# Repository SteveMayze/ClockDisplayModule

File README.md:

# ClockDisplayModule
A module to provide a 4x7 Segment display digital clock face

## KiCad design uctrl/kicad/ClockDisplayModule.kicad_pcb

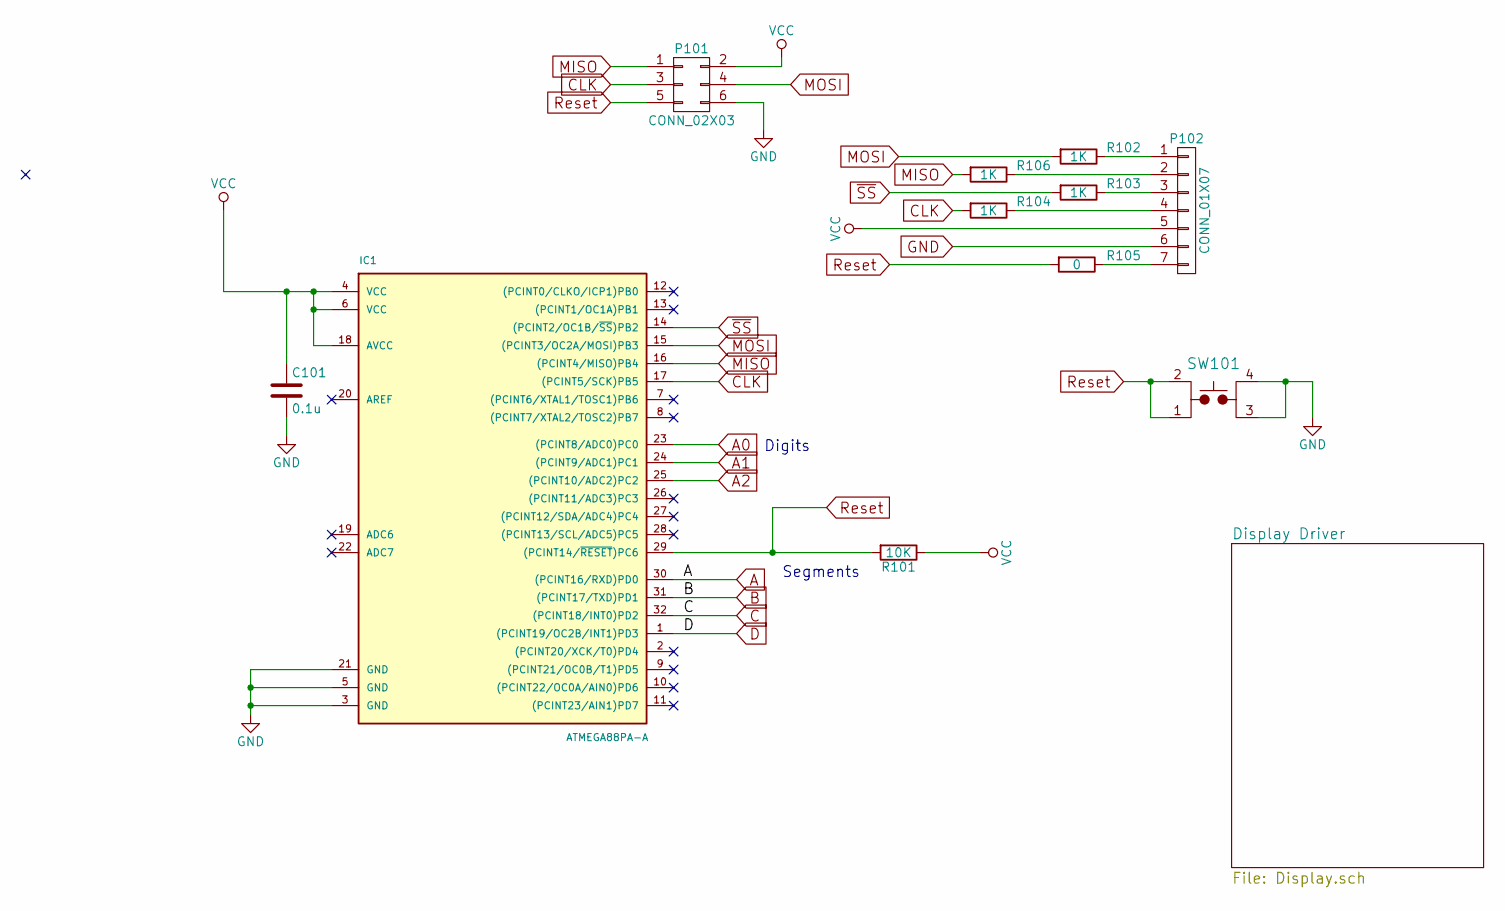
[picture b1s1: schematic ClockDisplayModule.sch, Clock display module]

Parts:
C101: 0.1u; C_0805
IC1: ATMEGA88PA-A; LQFP-32_7x7mm_Pitch0.8mm
P101: CONN_02X03; Pin_Header_Straight_2x03; MPN WS6G
P102: CONN_01X07; Pin_Header_Straight_1x07; Voltage Value; DigiKeyPN Value
R101: 10K; R_0805
R102, R103, R104, R106: 1K; R_0805
R105: 0; R_0805
SW101: TL3315NF160Q; PTS525SM15SMTR2LFS

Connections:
A: IC1.30 ((PCINT16/RXD)PD0); also elsewhere on the board
A0: IC1.23 ((PCINT8/ADC0)PC0); also elsewhere on the board
A1: IC1.24 ((PCINT9/ADC1)PC1); also elsewhere on the board
A2: IC1.25 ((PCINT10/ADC2)PC2); also elsewhere on the board
B: IC1.31 ((PCINT17/TXD)PD1); also elsewhere on the board
C: IC1.32 ((PCINT18/INT0)PD2); also elsewhere on the board
CLK: IC1.17 ((PCINT5/SCK)PB5), P101.3, R104.2
D: IC1.1 ((PCINT19/OC2B/INT1)PD3); also elsewhere on the board
GND: C101.2, IC1.3 (GND), IC1.5 (GND), IC1.21 (GND), P101.6, P102.6, SW101.3, SW101.4; also elsewhere on the board
MISO: IC1.16 ((PCINT4/MISO)PB4), P101.1, R106.2
MOSI: IC1.15 ((PCINT3/OC2A/MOSI)PB3), P101.4, R102.2
unnamed: P102.1, R102.1
unnamed: P102.2, R106.1
unnamed: P102.3, R103.1
unnamed: P102.4, R104.1
unnamed: P102.7, R105.1
Reset: IC1.29 ((PCINT14/~RESET~)PC6), P101.5, R101.2, R105.2, SW101.1, SW101.2
VCC: C101.1, IC1.4 (VCC), IC1.6 (VCC), IC1.18 (AVCC), P101.2, P102.5, R101.1; also elsewhere on the board
~SS: IC1.14 ((PCINT2/OC1B/~SS~)PB2), R103.2

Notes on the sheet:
Digits
Segments

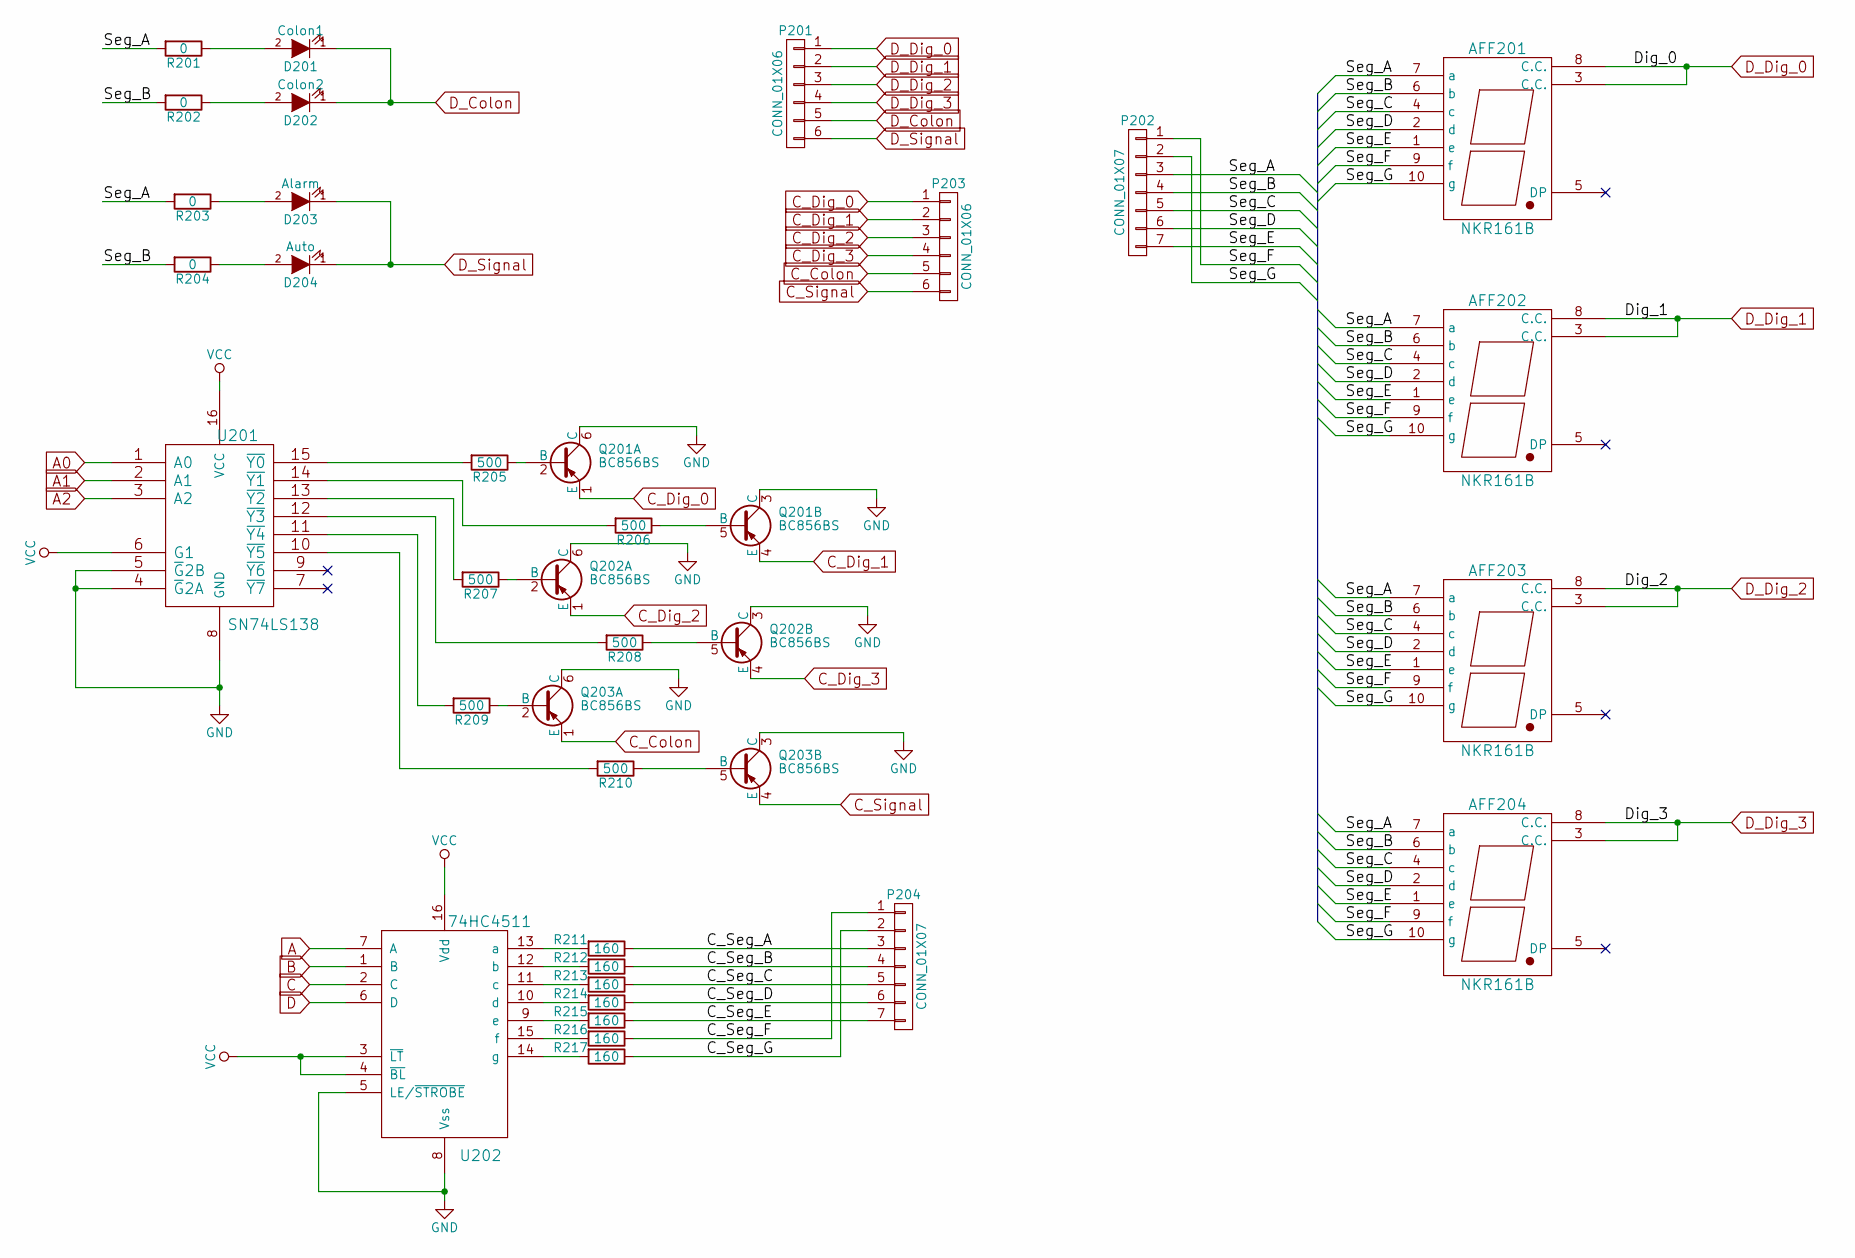
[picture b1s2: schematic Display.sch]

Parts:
AFF201, AFF202, AFF203, AFF204: NKR161B; 161_163_Series_extended; MPN NKR161B
D201: Colon1; LED-0805; MPN Value
D202: Colon2; LED-0805; MPN Value
D203: Alarm; LED-0805; MPN Value
D204: Auto; LED-0805; MPN Value
P201, P203: CONN_01X06; Pin_Header_Straight_1x06
P202, P204: CONN_01X07; Pin_Header_Straight_1x07
Q201, Q202, Q203: BC856BS; SOT-363; MPN BC856BS
R201, R202, R203, R204: 0; R_0805
R205, R206, R207, R208, R209, R210: 500; R_0805
R211, R212, R213, R214, R215, R216, R217: 160; R_0805
U201: SN74LS138; SOIC-16; MPN SN74LS138NSR
U202: 74HC4511; SOIC-16; MPN CD4511BNSR

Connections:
/Display Driver/C_Seg_A: P204.3, R211.1
/Display Driver/C_Seg_B: P204.4, R212.1
/Display Driver/C_Seg_C: P204.5, R213.1
/Display Driver/C_Seg_D: P204.6, R214.1
/Display Driver/C_Seg_E: P204.7, R215.1
/Display Driver/C_Seg_F: P204.1, R216.1
/Display Driver/C_Seg_G: P204.2, R217.1
/Display Driver/Seg_A: AFF201.7 (a), AFF202.7 (a), AFF203.7 (a), AFF204.7 (a), P202.3, R201.2, R203.2
/Display Driver/Seg_B: AFF201.6 (b), AFF202.6 (b), AFF203.6 (b), AFF204.6 (b), P202.4, R202.2, R204.2
/Display Driver/Seg_C: AFF201.4 (c), AFF202.4 (c), AFF203.4 (c), AFF204.4 (c), P202.5
/Display Driver/Seg_D: AFF201.2 (d), AFF202.2 (d), AFF203.2 (d), AFF204.2 (d), P202.6
/Display Driver/Seg_E: AFF201.1 (e), AFF202.1 (e), AFF203.1 (e), AFF204.1 (e), P202.7
/Display Driver/Seg_F: AFF201.9 (f), AFF202.9 (f), AFF203.9 (f), AFF204.9 (f), P202.1
/Display Driver/Seg_G: AFF201.10 (g), AFF202.10 (g), AFF203.10 (g), AFF204.10 (g), P202.2
A: U202.7 (A); also elsewhere on the board
A0: U201.1 (A0); also elsewhere on the board
A1: U201.2 (A1); also elsewhere on the board
A2: U201.3 (A2); also elsewhere on the board
B: U202.1 (B); also elsewhere on the board
C: U202.2 (C); also elsewhere on the board
C_Colon: P203.5, Q203.1 (E)
C_Dig_0: P203.1, Q201.1 (E)
C_Dig_1: P203.2, Q201.4 (E)
C_Dig_2: P203.3, Q202.1 (E)
C_Dig_3: P203.4, Q202.4 (E)
C_Signal: P203.6, Q203.4 (E)
D: U202.6 (D); also elsewhere on the board
D_Colon: D201.1 (K), D202.1 (K), P201.5
D_Dig_0: AFF201.3 (C.C.), AFF201.8 (C.C.), P201.1
D_Dig_1: AFF202.3 (C.C.), AFF202.8 (C.C.), P201.2
D_Dig_2: AFF203.3 (C.C.), AFF203.8 (C.C.), P201.3
D_Dig_3: AFF204.3 (C.C.), AFF204.8 (C.C.), P201.4
D_Signal: D203.1 (K), D204.1 (K), P201.6
GND: Q201.3 (C), Q201.6 (C), Q202.3 (C), Q202.6 (C), Q203.3 (C), Q203.6 (C), U201.4 (~G~2A), U201.5 (~G~2B), U201.8 (GND), U202.5 (LE/~STROBE), U202.8 (Vss); also elsewhere on the board
unnamed: D201.2 (A), R201.1
unnamed: D202.2 (A), R202.1
unnamed: D203.2 (A), R203.1
unnamed: D204.2 (A), R204.1
unnamed: Q201.2 (B), R205.1
unnamed: Q201.5 (B), R206.1
unnamed: Q202.2 (B), R207.1
unnamed: Q202.5 (B), R208.1
unnamed: Q203.2 (B), R209.1
unnamed: Q203.5 (B), R210.1
unnamed: R205.2, U201.15 (~Y0)
unnamed: R206.2, U201.14 (~Y1)
unnamed: R207.2, U201.13 (~Y2)
unnamed: R208.2, U201.12 (~Y3)
unnamed: R209.2, U201.11 (~Y4)
unnamed: R210.2, U201.10 (~Y5)
unnamed: R211.2, U202.13 (a)
unnamed: R212.2, U202.12 (b)
unnamed: R213.2, U202.11 (c)
unnamed: R214.2, U202.10 (d)
unnamed: R215.2, U202.9 (e)
unnamed: R216.2, U202.15 (f)
unnamed: R217.2, U202.14 (g)
VCC: U201.6 (G1), U201.16 (VCC), U202.3 (~LT), U202.4 (~BL), U202.16 (Vdd); also elsewhere on the board

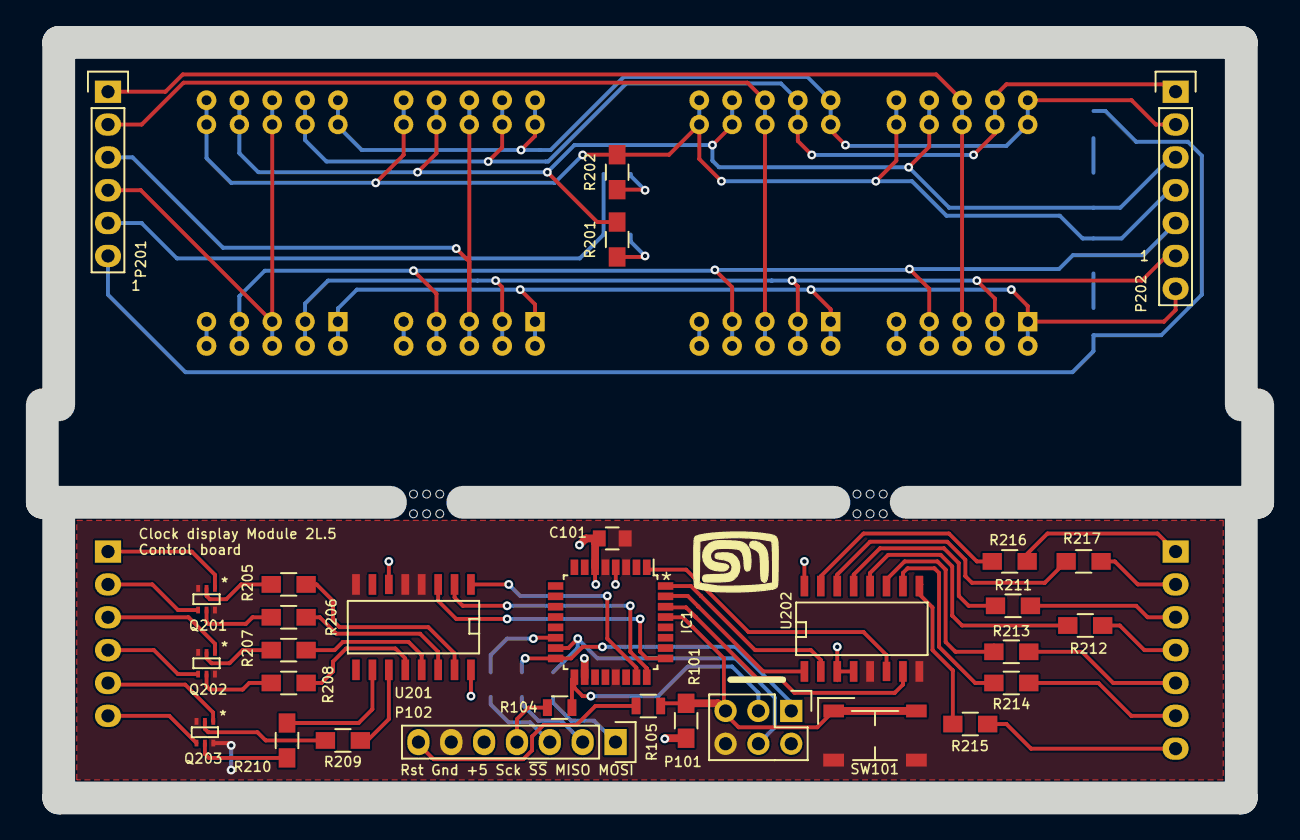
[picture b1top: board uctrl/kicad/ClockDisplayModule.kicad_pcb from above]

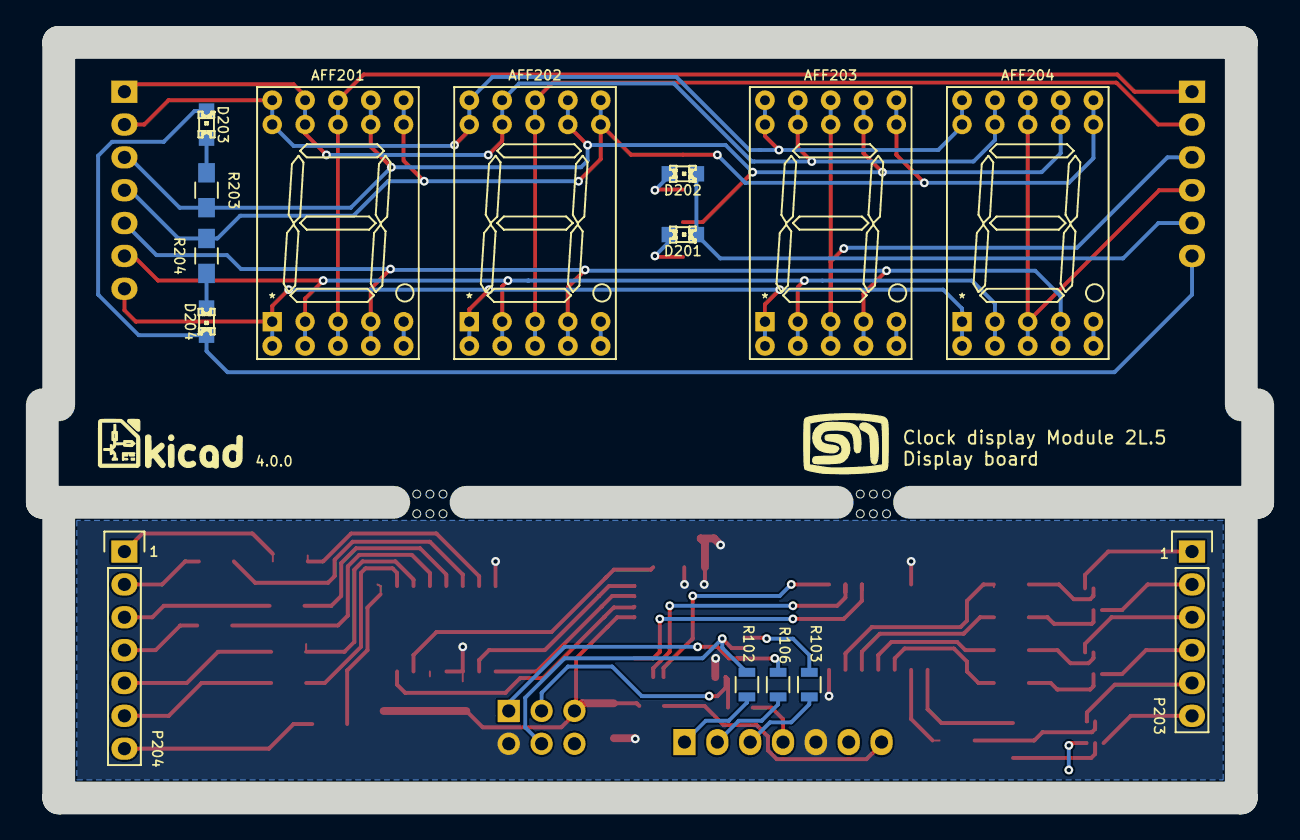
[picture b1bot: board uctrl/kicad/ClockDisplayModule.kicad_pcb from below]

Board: 2 copper layers, 94.0 x 58.4 mm, 47 parts (17 on the bottom side), 68 nets.

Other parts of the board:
LOGO1: LOGO; myLogo_basic_rounded_50
LOGO2: LOGO; kicad_logo

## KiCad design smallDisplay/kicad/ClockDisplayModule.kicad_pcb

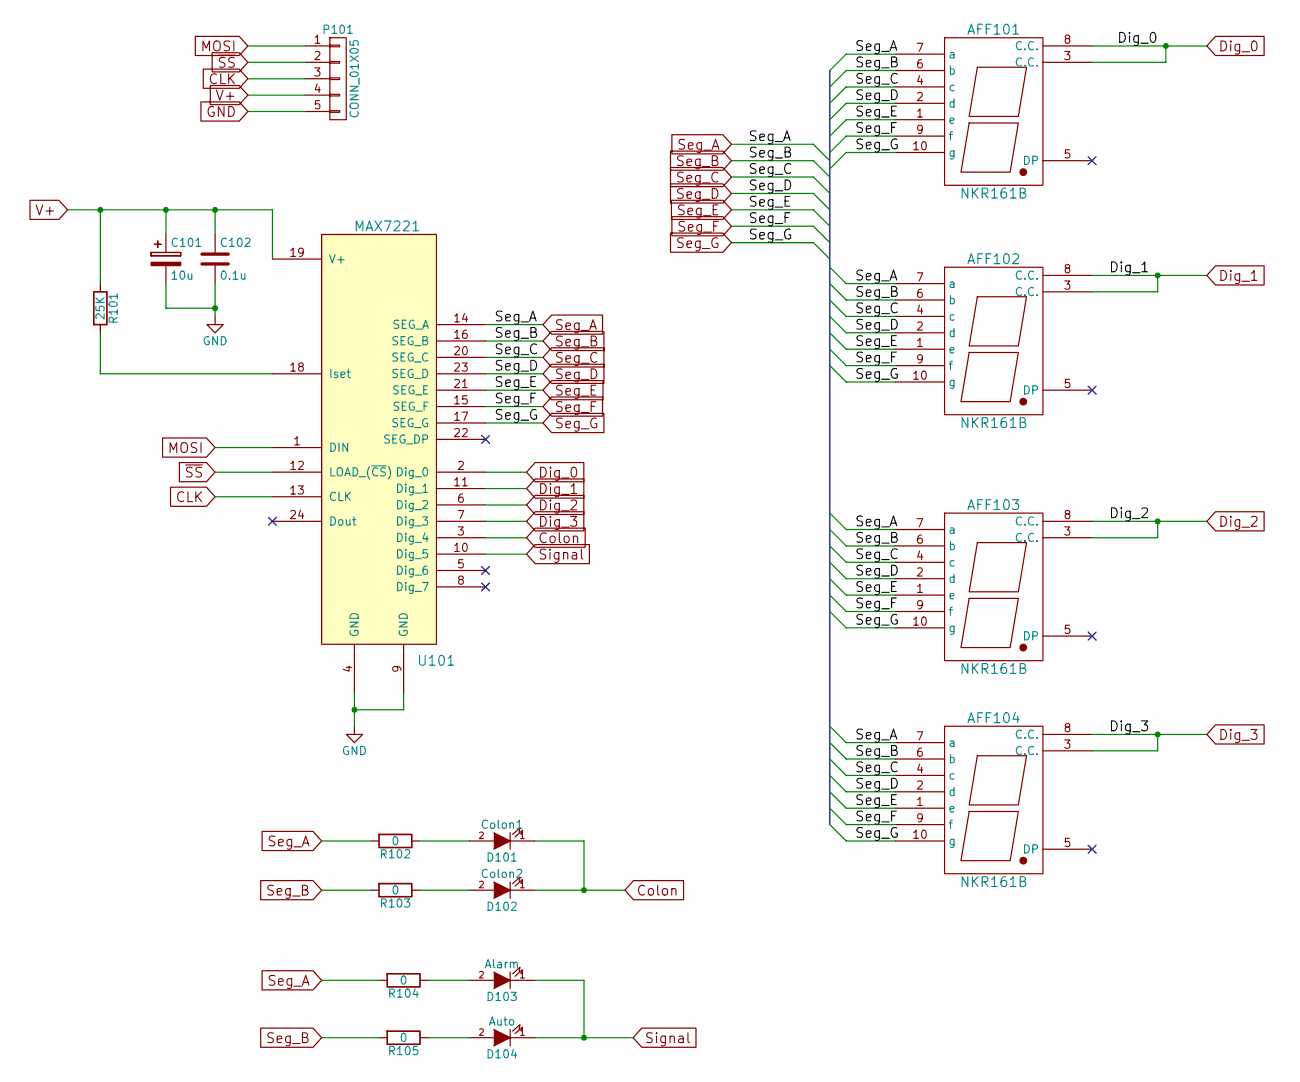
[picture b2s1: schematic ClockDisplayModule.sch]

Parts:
AFF101, AFF102, AFF103, AFF104: NKR161B; 161_163_Series; MPN NKR161B
C101: 10u; c_elec_4x5.8; MPN EEE-FK1C100R
C102: 0.1u; C_0805_HandSoldering
D101: Colon1; LED-0805; MPN Value
D102: Colon2; LED-0805; MPN Value
D103: Alarm; LED-0805; MPN Value
D104: Auto; LED-0805; MPN Value
P101: CONN_01X05; Pin_Header_Straight_1x05
R101: 25K; R_0805_HandSoldering
R102, R103, R104, R105: 0; R_0805_HandSoldering
U101: MAX7221; SOIC-24; MPN MAX7221

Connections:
CLK: P101.3, U101.13 (CLK)
Colon: D101.1 (K), D102.1 (K), U101.3 (Dig_4)
Dig_0: AFF101.3 (C.C.), AFF101.8 (C.C.), U101.2 (Dig_0)
Dig_1: AFF102.3 (C.C.), AFF102.8 (C.C.), U101.11 (Dig_1)
Dig_2: AFF103.3 (C.C.), AFF103.8 (C.C.), U101.6 (Dig_2)
Dig_3: AFF104.3 (C.C.), AFF104.8 (C.C.), U101.7 (Dig_3)
GND: C101.2, C102.2, P101.5, U101.4 (GND), U101.9 (GND)
MOSI: P101.1, U101.1 (DIN)
unnamed: D101.2 (A), R102.1
unnamed: D102.2 (A), R103.1
unnamed: D103.2 (A), R104.1
unnamed: D104.2 (A), R105.1
unnamed: R101.2, U101.18 (Iset)
Seg_A: AFF101.7 (a), AFF102.7 (a), AFF103.7 (a), AFF104.7 (a), R102.2, R104.2, U101.14 (SEG_A)
Seg_B: AFF101.6 (b), AFF102.6 (b), AFF103.6 (b), AFF104.6 (b), R103.2, R105.2, U101.16 (SEG_B)
Seg_C: AFF101.4 (c), AFF102.4 (c), AFF103.4 (c), AFF104.4 (c), U101.20 (SEG_C)
Seg_D: AFF101.2 (d), AFF102.2 (d), AFF103.2 (d), AFF104.2 (d), U101.23 (SEG_D)
Seg_E: AFF101.1 (e), AFF102.1 (e), AFF103.1 (e), AFF104.1 (e), U101.21 (SEG_E)
Seg_F: AFF101.9 (f), AFF102.9 (f), AFF103.9 (f), AFF104.9 (f), U101.15 (SEG_F)
Seg_G: AFF101.10 (g), AFF102.10 (g), AFF103.10 (g), AFF104.10 (g), U101.17 (SEG_G)
Signal: D103.1 (K), D104.1 (K), U101.10 (Dig_5)
V+: C101.1, C102.1, P101.4, R101.1, U101.19 (V+)
~SS: P101.2, U101.12 (LOAD_(~CS))

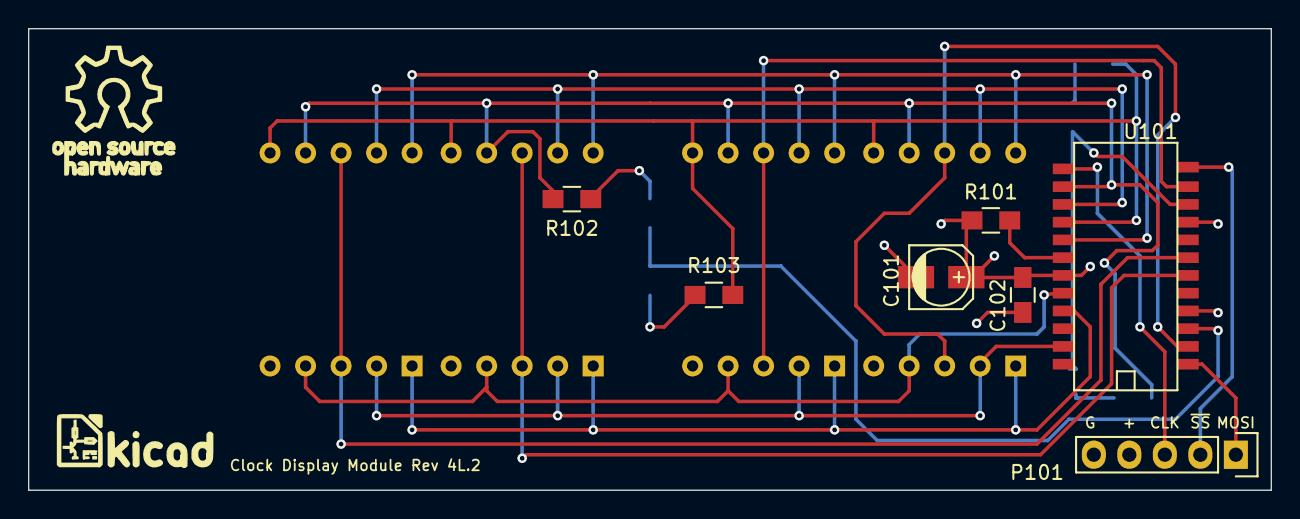
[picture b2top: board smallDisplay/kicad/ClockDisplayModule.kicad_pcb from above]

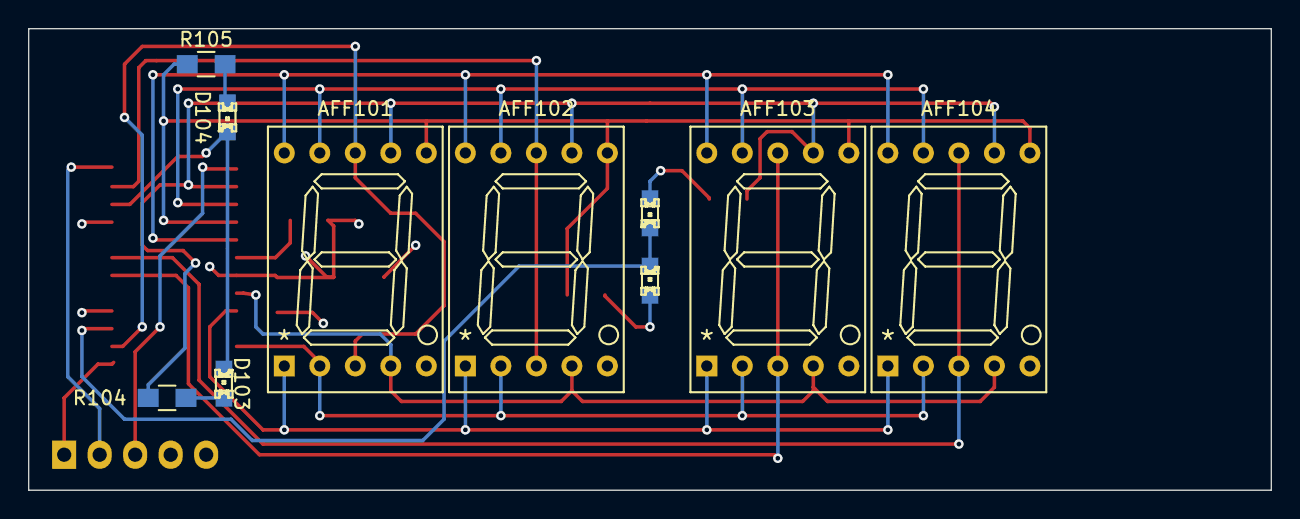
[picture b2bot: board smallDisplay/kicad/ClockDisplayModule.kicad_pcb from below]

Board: 4 copper layers, 88.9 x 33.0 mm, 17 parts (10 on the bottom side), 23 nets.

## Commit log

2015-06-07 Initial schematic
2015-06-08 Removed the backup files
2015-06-08 Library correction and rework of schematic
2015-06-08 Initial layout
2015-06-09 Small changes to schematic
2015-06-09 Initial layout before routing
2015-06-10 Layout complete and board ordered
2015-06-10 page settings change
2015-06-16 Initial trail of the layout. The given board is not big enough
2015-06-16 Initial schematic for the controller based display driver
2015-06-21 Correction to the Conrad part numbers
    Correction to the Conrad part numbers for the 7 Segment displays
2015-06-23 Preperation for layout
2015-06-24 Started layout
2015-06-25 Updated the layout for the controller side
2015-06-27 Board layout completed
2015-06-27 Added annotiations and logo
2015-06-27 refined the logo image
2015-06-27 Added breakout for the board
2015-06-28 Updated the logo
2015-07-01 More refinements and updates to logos
2015-07-01 Final logo added
2015-07-04 Changes to the gerbers
2015-07-04 Added a BOM
2015-07-04 Added some Conrad part numbers
2015-07-07 Added initial firmware code
2015-07-08 Initial test firmware created
    The blinker is just a simple program to verify the ISP. The simpleCheck
    can communicate to the clock module and the display module.
2015-07-15 Added the firmware for the MAX7221 display module
2015-07-15 Added BOM
2015-07-21 small correction
2015-07-21 Updated the max7221 datasheet
2015-07-21 Added some current usage results for the display
2015-07-23 Simple Blinker for the breadboard test
2015-07-24 Added first check blinker for the uControl display module
2015-07-24 Correction to microcontroller footprint
2015-07-24 Created the kicad-rev_2 directory to provide the corrected board without the LED section
2015-08-22 Corrections to the layout based on testing
2015-08-23 Added some firmware for the intial testing
2015-08-29 checkin before moving to Vagrant
2015-09-08 Update to the driver code to a working model
2015-09-08 Update to the firmware as a working example
2015-09-09 Set PORTD to &H0A to swtich off all segments before changing the value
2015-09-20 Updated they layout
2015-12-03 Updated display driver to support power mode, colons and indicators better
2015-12-03 Updated main project with fixes from issues discovered when brining up the board
2015-12-03 Updated the footprint for the reset switch
2015-12-08 Created Gerbers and orderd 2l.3 (REV3) of the board
2015-12-10 Enhancements to the micro controlled display firmware
2015-12-12 Removed the kicad cache from the .gitignore
2015-12-12 moved the smallDisplay branch to its own directory
2015-12-12 Moved the largeDisplay to its own directory
2015-12-12 Moved the UCtrl_small branch to the ucrl directory
2015-12-12 Revert "moved the smallDisplay branch to its own directory"
    This reverts commit b078eeab5859ec3d63b3dc095890a6a090f9175d.
2015-12-12 Revert "Moved the largeDisplay to its own directory"
    This reverts commit fb9d403b8ae12a440a5377ca2228b0d60af6e2e4.
2015-12-12 Revert "Moved the UCtrl_small branch to the ucrl directory"
    This reverts commit 840599a76f67236bf795ed3e24a3de87f15bbceb.
2015-12-12 Copied the smallDisplay branch to its own directory
2015-12-12 Copied the largeDisplay label to its own directory
2015-12-12 Copied the UCtrl_small to the uctrl directory
2015-12-12 Copied UCtrl_small branch to the uctl directory
2015-12-12 Revert "Copied UCtrl_small branch to the uctl directory"
    This reverts commit c9353255f9380f72b0e1684e404d0a0f8c6bfb7f.
2015-12-12 Final clean up of merging the branches to their own directories
2015-12-12 Updated the reset switch symbol and footprint
2015-12-13 Small update to the config spi
2015-12-13 Tweaking the SPI config
2015-12-31 An intermediate save of code that is basically working
2015-12-31 Register addresses need to have bit 7 set
2016-01-04 Cleaned up the timer specifications for the 10th second timer
2016-01-14 Correction to segments F and G!
2016-01-24 Added a datasheet for a new potential 7-segment
2016-01-24 Updated the 'blink' timer to 2Hz rather than 10Hz
2016-03-03 Updated the seven segment foot print and added the mounting tabs
2016-03-03 Started routing the modified board
2016-03-05 Finished routing of revision 4
2016-03-06 Cleaned up a couple of references on the board
2016-03-06 Added the data sheet for the new seven sigment display
2016-03-06 save of dot pro file
2016-03-06 Generated Gerbers for 2L4
2016-07-28 Updated the revision number
2016-07-28 Altered the pin header to include MISO and to simplify connection to to the main board.
2016-07-31 Created 2L_5 Gerbers and ordered stensils and bgoards
2016-10-16 Generated the BOM for analysis
2016-10-16 Firmware testing
